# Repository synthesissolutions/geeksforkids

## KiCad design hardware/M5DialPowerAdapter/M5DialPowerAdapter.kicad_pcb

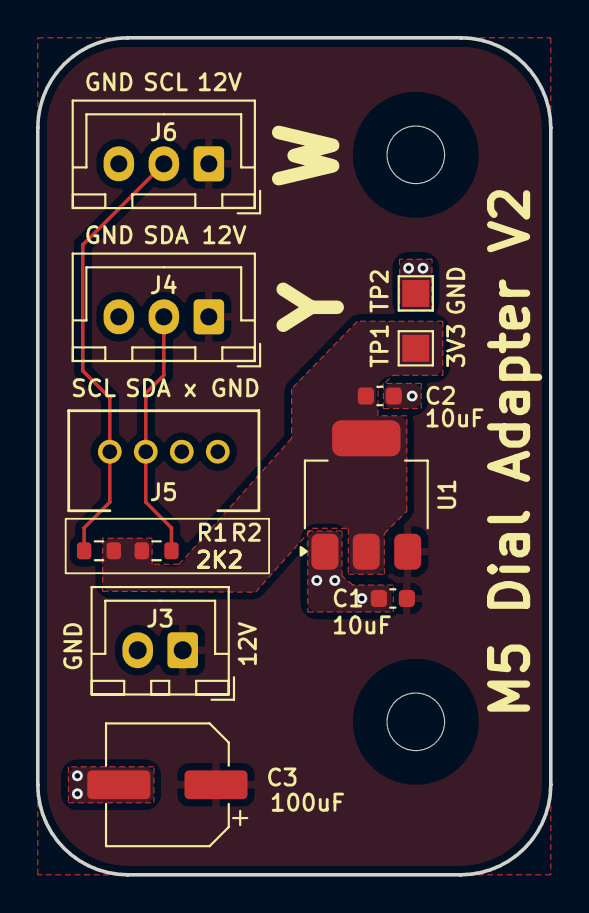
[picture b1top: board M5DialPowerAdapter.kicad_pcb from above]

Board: 2 copper layers, 28.5 x 46.5 mm, 14 parts (0 on the bottom side), 5 nets.

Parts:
C1, C2: 10uF; C_0603_1608Metric
C3: 100uF; CP_Elec_6.3x7.7
H1, H2: MountingHole_3.2mm_M3
J3: M5Dial Power; JST_XH_B2B-XH-A_1x02_P2.50mm_Vertical
J4: JST XH SCA; JST_XH_B3B-XH-A_1x03_P2.50mm_Vertical
J5: Grove I2C; CONN_110990030_SEE
J6: JST XH SCL; JST_XH_B3B-XH-A_1x03_P2.50mm_Vertical
R1, R2: 2K2; R_0603_1608Metric
TP1: 3V3; TestPoint_Pad_1.5x1.5mm
TP2: GND; TestPoint_Pad_1.5x1.5mm
U1: AMS1117-3.3; SOT-223-3_TabPin2

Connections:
+3V3: C2.1, R1.2, R2.2, TP1.1, U1.2 (VO)
+12V: C1.1, C3.1, J3.1, J4.1, J6.1, U1.3 (VI)
GND: C1.2, C2.2, C3.2, J3.2, J4.3, J5.4, J6.3, TP2.1, U1.1 (GND)
SCL: J5.1, J6.2, R1.1
SDA: J4.2, J5.2, R2.1

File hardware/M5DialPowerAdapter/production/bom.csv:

Designator,Footprint,Quantity,Value,LCSC Part #
"C1, C2",0603,2,10uF,C96446
C3,CP_Elec_6.3x7.7,1,100uF,C179802
J3,JST_XH_B2B-XH-A_1x02_P2.50mm_Vertical,1,M5Dial Power,
J4,JST_XH_B3B-XH-A_1x03_P2.50mm_Vertical,1,JST XH SCA,
J5,CONN_110990030_SEE,1,Grove I2C,
J6,JST_XH_B3B-XH-A_1x03_P2.50mm_Vertical,1,JST XH SCL,
"R1, R2",0603,2,2K2,C4190
TP1,TestPoint_Pad_1.5x1.5mm,1,3V3,
TP2,TestPoint_Pad_1.5x1.5mm,1,GND,
U1,SOT-223-3_TabPin2,1,AMS1117-3.3,C5120765

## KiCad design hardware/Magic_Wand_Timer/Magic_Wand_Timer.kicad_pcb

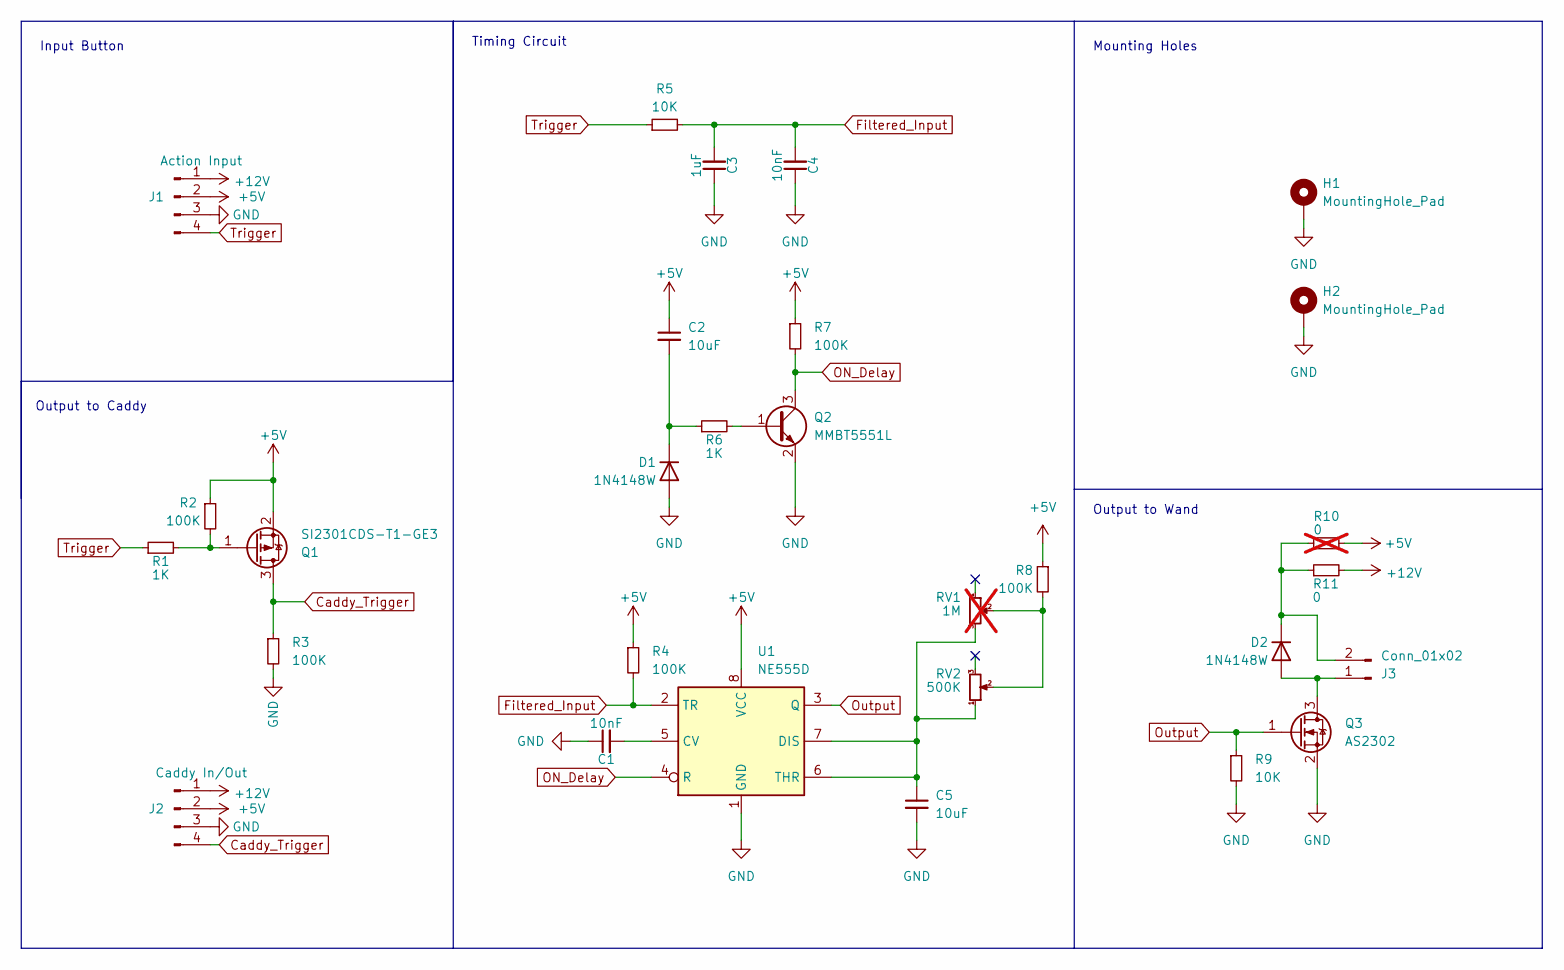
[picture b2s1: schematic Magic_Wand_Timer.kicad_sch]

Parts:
C1, C4: 10nF; C_0805_2012Metric; MPN C1710
C2, C5: 10uF; C_0805_2012Metric; MPN C15850
C3: 1uF; C_0805_2012Metric; MPN C28323
D1, D2: 1N4148W; D_SOD-123; MPN C81598
H1, H2: MountingHole_Pad; MountingHole_2.5mm_Pad
J1: Action Input; JST_XH_B4B-XH-A_1x04_P2.50mm_Vertical
J2: Caddy In/Out; JST_XH_B4B-XH-A_1x04_P2.50mm_Vertical
J3: Conn_01x02; JST_XH_B2B-XH-A_1x02_P2.50mm_Vertical
Q1: SI2301CDS-T1-GE3; SOT-23; MPN C10487
Q2: MMBT5551L; SOT-23; MPN C2145
Q3: AS2302; SOT-23; MPN C20917
R1, R6: 1K; R_0805_2012Metric; MPN C17513
R2, R3, R4, R7, R8: 100K; R_0805_2012Metric; MPN C149504
R5, R9: 10K; R_0805_2012Metric; MPN C17414
R10: 0; R_0805_2012Metric; MPN C17477; not fitted
R11: 0; R_0805_2012Metric; MPN C17477
RV1: 1M; Potentiometer_Piher_PT-6-V_Vertical; not fitted
RV2: 500K; Potentiometer_Bourns_TC33X_Vertical; MPN C128558
U1: NE555D; SOIC-8_3.9x4.9mm_P1.27mm; MPN C7593

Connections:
+5V: C2.1, J1.2, J2.2, Q1.2 (S), R2.1, R4.1, R7.1, R8.1, R10.1, U1.8 (VCC)
+12V: J1.1, J2.1, R11.2
Caddy_Trigger: J2.4, Q1.3 (D), R3.1
Filtered_Input: C3.2, C4.2, R4.2, R5.2, U1.2 (TR)
GND: C1.1, C3.1, C4.1, C5.2, D1.2 (A), H1.1, H2.1, J1.3, J2.3, Q2.2 (E), Q3.2 (S), R3.2, R9.2, U1.1 (GND)
unnamed: C2.2, D1.1 (K), R6.1
unnamed: D2.2 (A), J3.1, Q3.3 (D)
unnamed: D2.1 (K), J3.2, R10.2, R11.1
unnamed: Q1.1 (G), R1.2, R2.2
unnamed: Q2.1 (B), R6.2
unnamed: R8.2, RV1.2, RV2.2
unnamed: C1.2, U1.5 (CV)
unnamed: C5.1, RV1.3, RV2.1, U1.6 (THR), U1.7 (DIS)
ON_Delay: Q2.3 (C), R7.2, U1.4 (R)
Output: Q3.1 (G), R9.1, U1.3 (Q)
Trigger: J1.4, R1.1, R5.1

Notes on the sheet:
Timing Circuit
Mounting Holes
Output to Wand
Input Button
Output to Caddy

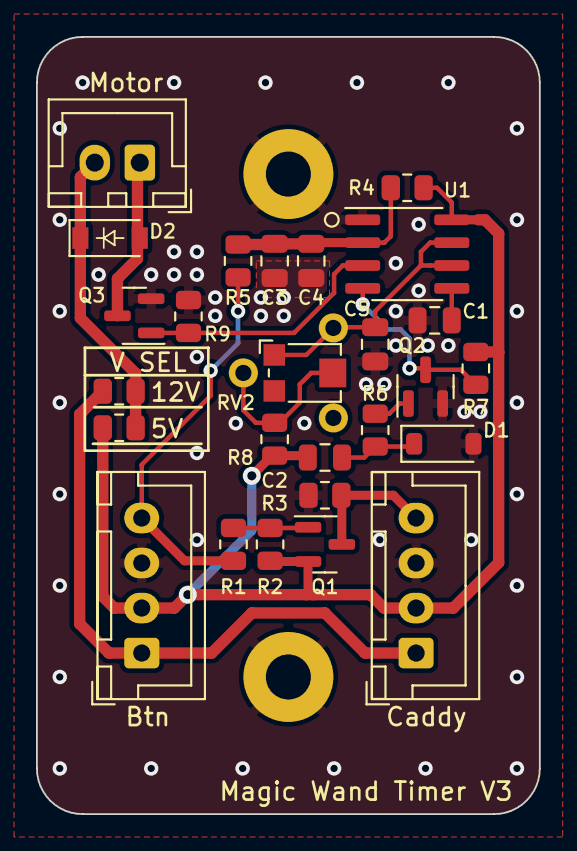
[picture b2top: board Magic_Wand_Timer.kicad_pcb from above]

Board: 2 copper layers, 27.9 x 43.2 mm, 29 parts (1 on the bottom side), 16 nets.

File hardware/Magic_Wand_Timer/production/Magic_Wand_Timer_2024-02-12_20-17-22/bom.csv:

Designator,Footprint,Quantity,Value,LCSC Part #
"C1, C4",0805,2,10nF,C1710
"C2, C5",0805,2,10uF,C15850
C3,0805,1,1uF,C28323
"D1, D2",D_SOD-123,2,1N4148W,C81598
"H1, H2",MountingHole_2.5mm_Pad,2,MountingHole_Pad,
J3,JST_XH_B2B-XH-A_1x02_P2.50mm_Vertical,1,Conn_01x02,
Q1,SOT-23,1,SI2301CDS-T1-GE3,C10487
Q2,SOT-23,1,MMBT5551L,C2145
Q3,SOT-23,1,AS2302,C20917
"R1, R6",0805,2,1K,C17513
R11,0805,1,0,C17477
"R2, R3, R4, R7, R8",0805,5,100K,C149504
"R5, R9",0805,2,10K,C17414
RV1,Potentiometer_Piher_PT-6-V_Vertical,1,1M,
RV2,Potentiometer_Bourns_TC33X_Vertical,1,500K,C128558
U1,SOIC-8_3.9x4.9mm_P1.27mm,1,NE555D,C7593

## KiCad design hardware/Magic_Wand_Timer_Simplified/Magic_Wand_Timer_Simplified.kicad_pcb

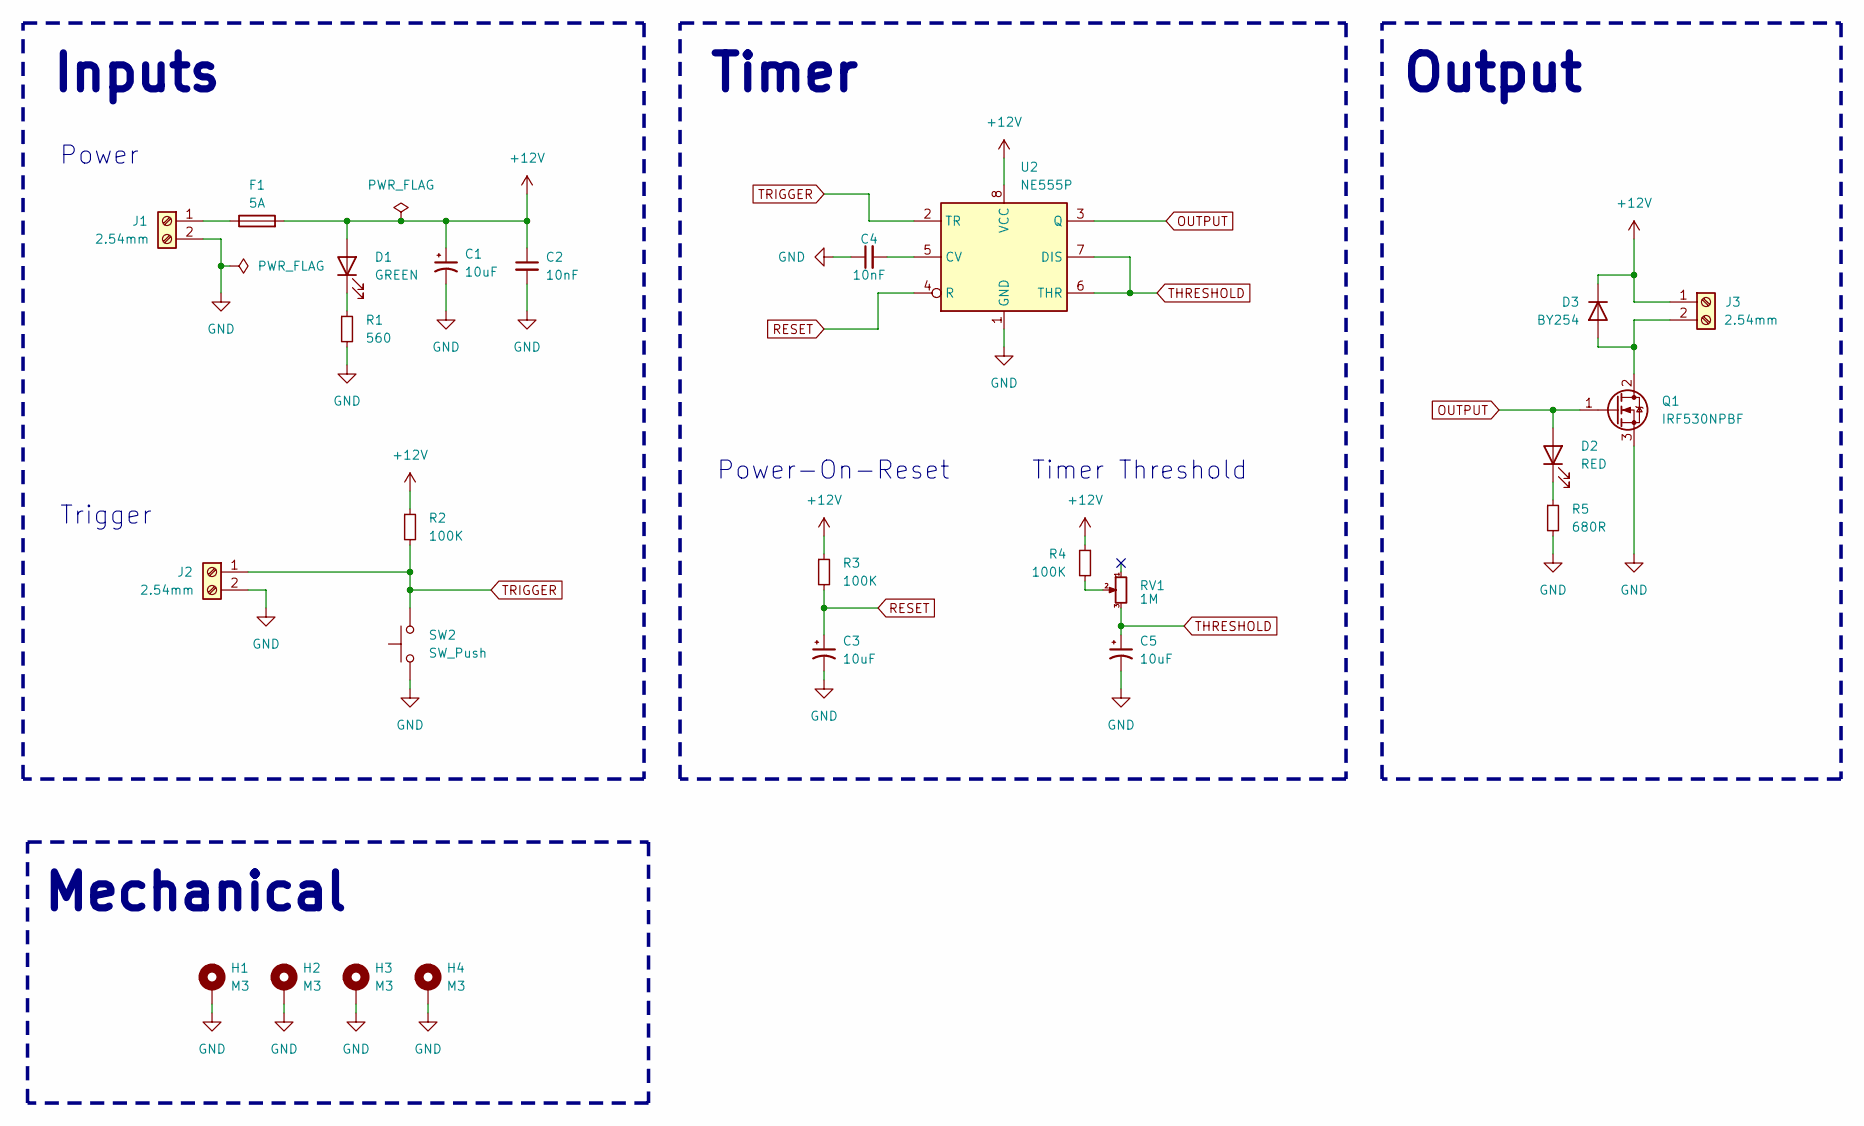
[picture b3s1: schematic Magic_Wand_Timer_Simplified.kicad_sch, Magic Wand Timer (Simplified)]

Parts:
C1, C3, C5: 10uF; C_Radial_D5.0mm_H11.0mm_P2.00mm; MPN C503219
C2, C4: 10nF; C_Disc_D3.8mm_W2.6mm_P2.50mm; MPN C2832505
D1: GREEN; LED_D5.0mm_Clear
D2: RED; LED_D5.0mm_Clear
D3: BY254; D_DO-201AD_P12.70mm_Horizontal; MPN C5148433
F1: 5A; Fuseholder_Clip-5x20mm_Littelfuse_111_Lateral_P18.80x5.00mm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; MPN C142664 + 2x C151075
H1, H2, H3, H4: M3; MountingHole_3.2mm_M3_Pad_Via
J1, J2, J3: 2.54mm; TerminalBlock_bornier-2_P5.08mm
Q1: IRF530NPBF; TO-220-3_Horizontal_TabDown; MPN C2565
R1: 560; R_Axial_DIN0309_L9.0mm_D3.2mm_P12.70mm_Horizontal
R2, R3, R4: 100K; R_Axial_DIN0309_L9.0mm_D3.2mm_P12.70mm_Horizontal
R5: 680R; R_Axial_DIN0309_L9.0mm_D3.2mm_P12.70mm_Horizontal
RV1: 1M; Potentiometer_Bourns_3386F_Vertical
SW2: SW_Push; SW_PUSH_6mm
U2: NE555P; DIP-8_W7.62mm; MPN C20616346

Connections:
+12V: C1.1, C2.1, D1.2 (A), D3.1 (K), F1.2, J3.1, R2.1, R3.1, R4.1, U2.8 (VCC)
GND: C1.2, C2.2, C3.2, C4.1, C5.2, H1.1, H2.1, H3.1, H4.1, J1.2, J2.2, Q1.3 (S), R1.2, R5.2, SW2.1, U2.1 (GND)
unnamed: D1.1 (K), R1.1
unnamed: D2.1 (K), R5.1
unnamed: D3.2 (A), J3.2, Q1.2 (D)
unnamed: F1.1, J1.1
unnamed: R4.2, RV1.2
unnamed: C4.2, U2.5 (CV)
OUTPUT: D2.2 (A), Q1.1 (G), U2.3 (Q)
RESET: C3.1, R3.2, U2.4 (R)
THRESHOLD: C5.1, RV1.3, U2.6 (THR), U2.7 (DIS)
TRIGGER: J2.1, R2.2, SW2.2, U2.2 (TR)

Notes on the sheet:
Inputs
Timer
Timer Threshold
Power
Mechanical
Output
Trigger
Power-On-Reset

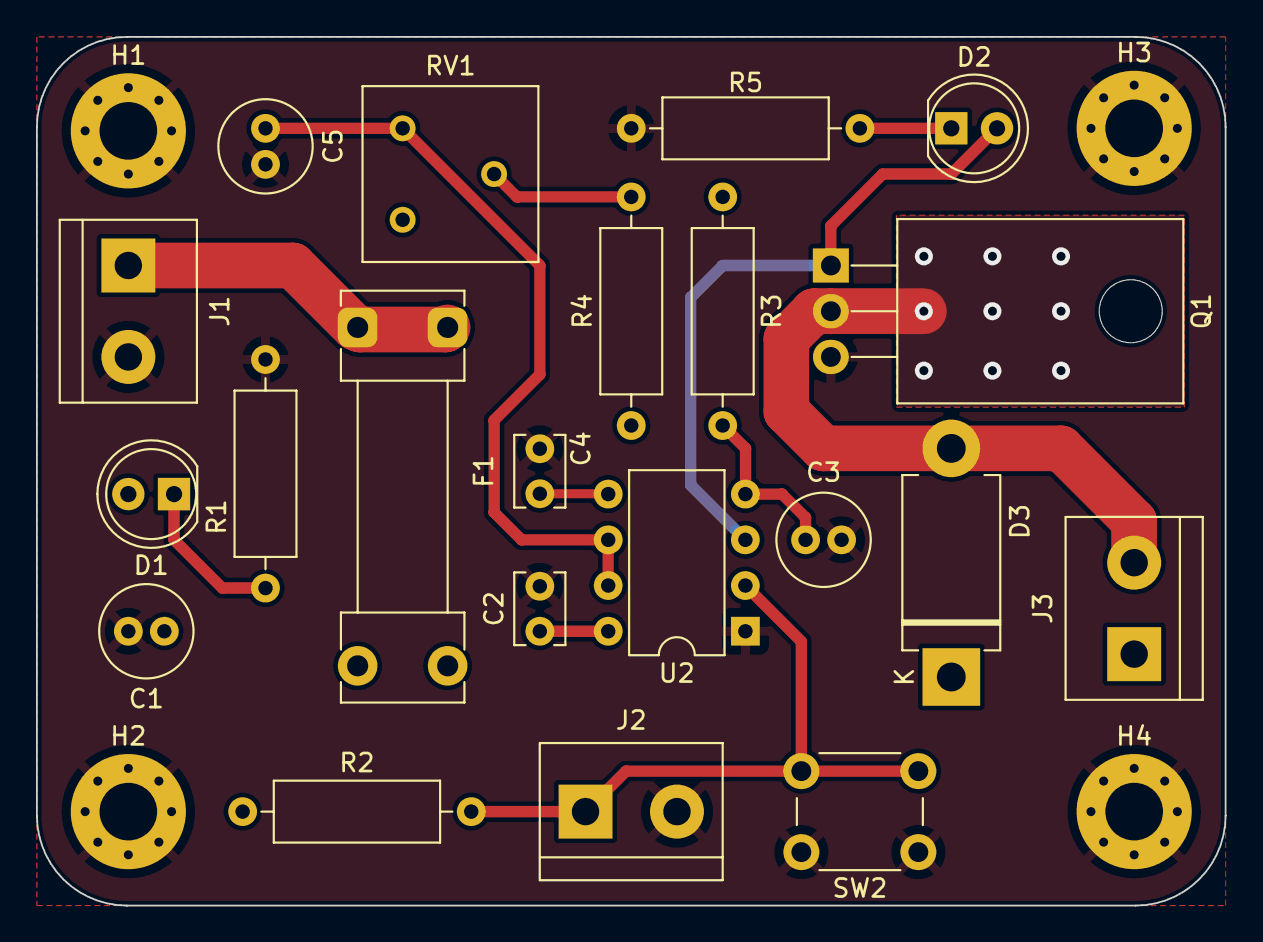
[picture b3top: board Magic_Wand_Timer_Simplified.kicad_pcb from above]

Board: 4 copper layers, 66.0 x 48.3 mm, 25 parts (0 on the bottom side), 12 nets.

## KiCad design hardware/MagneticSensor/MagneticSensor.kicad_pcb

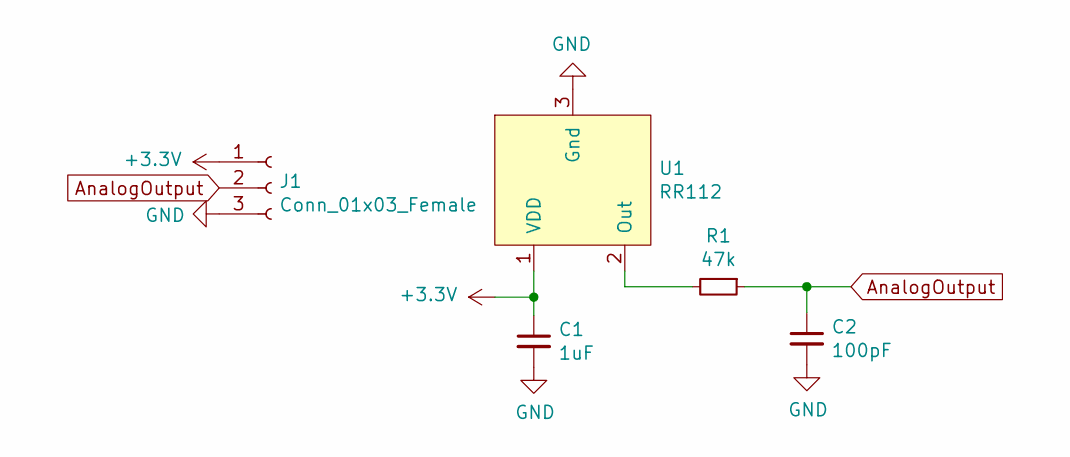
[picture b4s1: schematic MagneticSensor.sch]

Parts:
C1: 1uF; C_0805_2012Metric_Pad1.15x1.40mm_HandSolder
C2: 100pF; C_0805_2012Metric_Pad1.15x1.40mm_HandSolder
J1: Conn_01x03_Female; PinHeader_1x03_P2.54mm_Vertical
R1: 47k; R_0805_2012Metric_Pad1.15x1.40mm_HandSolder
U1: RR112; SOT-23_Handsoldering

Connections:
+3V3: C1.1, J1.1, U1.1 (VDD)
AnalogOutput: C2.1, J1.2, R1.1
GND: C1.2, C2.2, J1.3, U1.3 (Gnd)
unnamed: R1.2, U1.2 (Out)

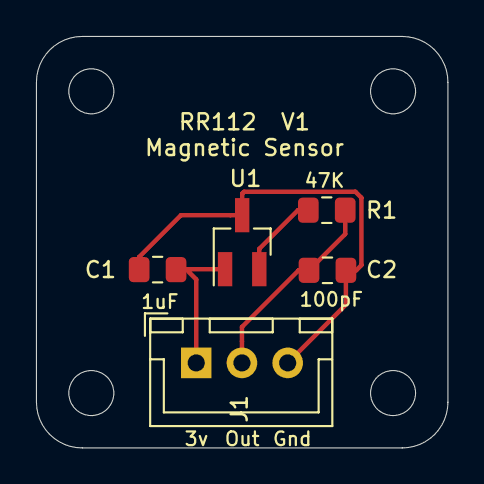
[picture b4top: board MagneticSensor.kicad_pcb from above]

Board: 2 copper layers, 22.9 x 22.9 mm, 5 parts (0 on the bottom side), 4 nets.

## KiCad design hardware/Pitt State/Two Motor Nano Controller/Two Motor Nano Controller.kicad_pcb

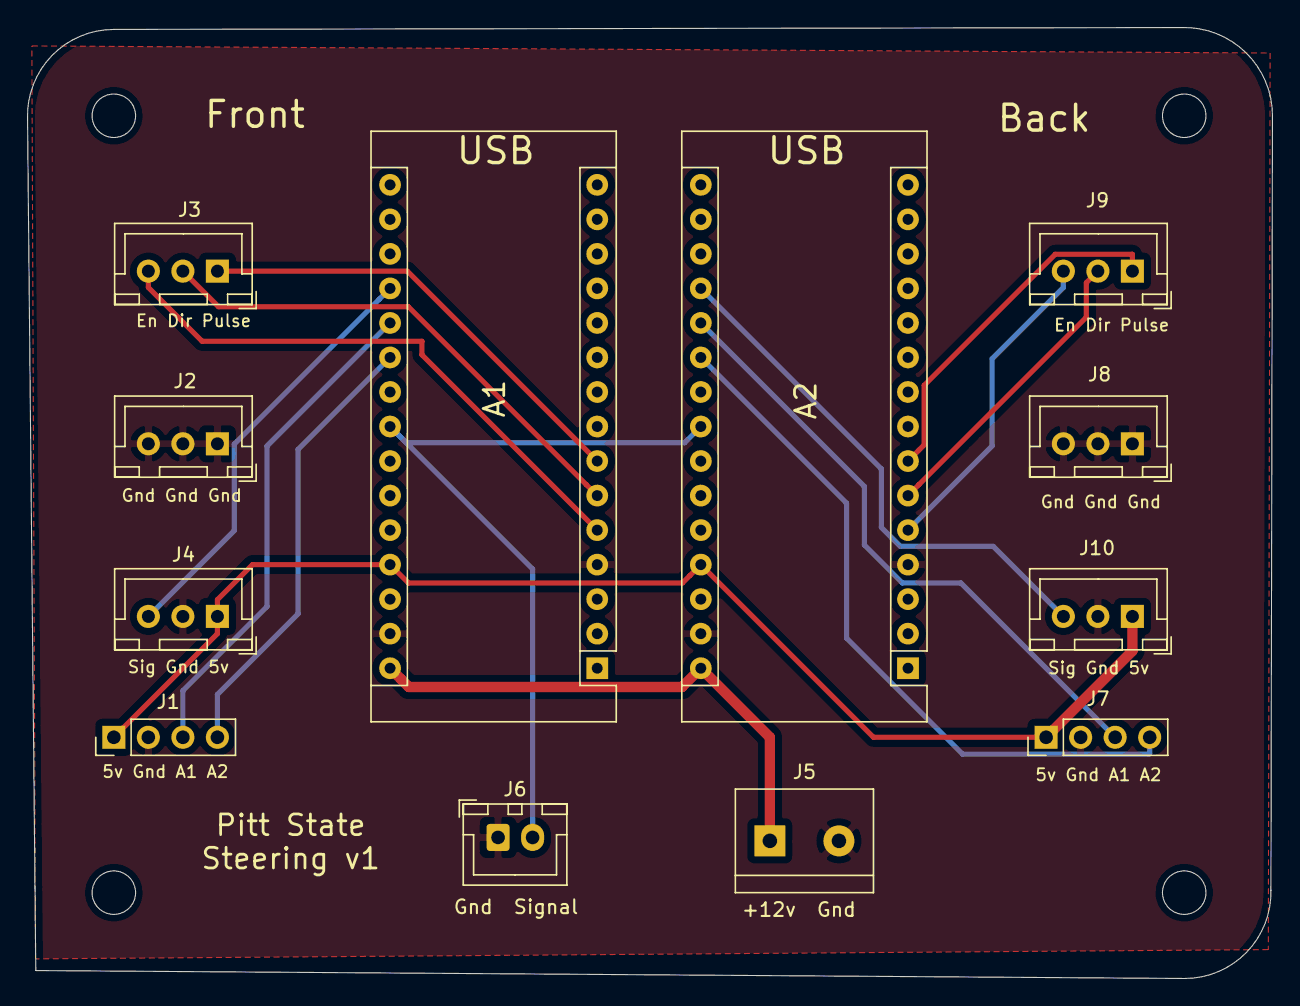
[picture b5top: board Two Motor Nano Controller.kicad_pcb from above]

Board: 2 copper layers, 91.6 x 70.0 mm, 12 parts (0 on the bottom side), 16 nets.

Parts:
A1, A2: Arduino_Nano_v3.x; Arduino_Nano
J1: Additiona Inputs Front; PinHeader_1x04_P2.54mm_Vertical
J2, J8: Stepper Minus Front; JST_XH_B3B-XH-A_1x03_P2.54mm_Vertical
J3: Stepper Plus Front; JST_XH_B3B-XH-A_1x03_P2.54mm_Vertical
J4, J10: Limit Switch Front; JST_XH_B3B-XH-A_1x03_P2.54mm_Vertical
J5: 12v Power; TerminalBlock_bornier-2_P5.08mm
J6: Analog Steering; JST_XH_B2B-XH-A_1x02_P2.54mm_Vertical
J7: Additiona Inputs Back; PinHeader_1x04_P2.54mm_Vertical
J9: Stepper Plus Back; JST_XH_B3B-XH-A_1x03_P2.54mm_Vertical

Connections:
+5V: A1.27, A2.27, J1.1, J4.1, J7.1, J10.1
+12V: A1.30, A2.30, J5.1
A1Back: A2.20, J7.3
A1Front: A1.20, J1.3
A2Back: A2.21, J7.4
A2Front: A1.21, J1.4
DirBack: A2.6, J9.2
DirFront: A1.6, J3.2
EnableBack: A2.5, J9.3
EnableFront: A1.5, J3.3
GND: A1.4, A1.29, A2.4, A2.29, J1.2, J2.1, J2.2, J2.3, J4.2, J5.2, J6.1, J7.2, J8.1, J8.2, J8.3, J10.2
LimitSwitchBack: A2.19, J10.3
LimitSwitchFront: A1.19, J4.3
PulseBack: A2.7, J9.1
PulseFront: A1.7, J3.1
SteeringSignal: A1.23, A2.23, J6.2

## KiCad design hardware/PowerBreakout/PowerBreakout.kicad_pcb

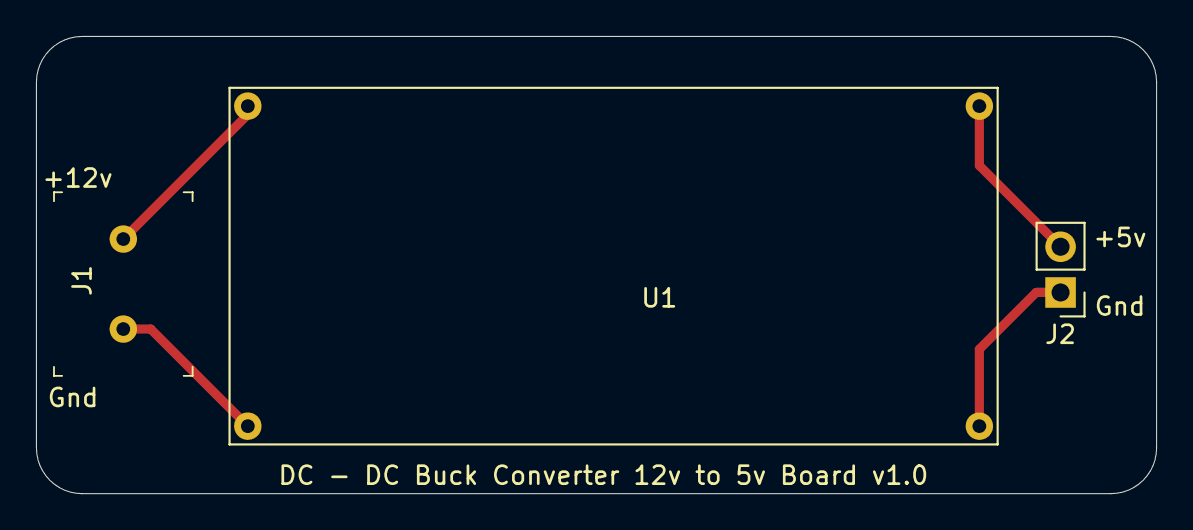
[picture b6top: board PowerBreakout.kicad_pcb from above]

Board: 2 copper layers, 62.2 x 25.4 mm, 3 parts (0 on the bottom side), 4 nets.

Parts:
J1: Screw_Terminal_01x02; Term_Block_1x2_P5mm
J2: Conn_01x02_Male; PinHeader_1x02_P2.54mm_Vertical
U1: LM2596Adj

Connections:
unnamed: J1.1, U1.2
unnamed: J1.2, U1.1
unnamed: J2.1, U1.4
unnamed: J2.2, U1.3

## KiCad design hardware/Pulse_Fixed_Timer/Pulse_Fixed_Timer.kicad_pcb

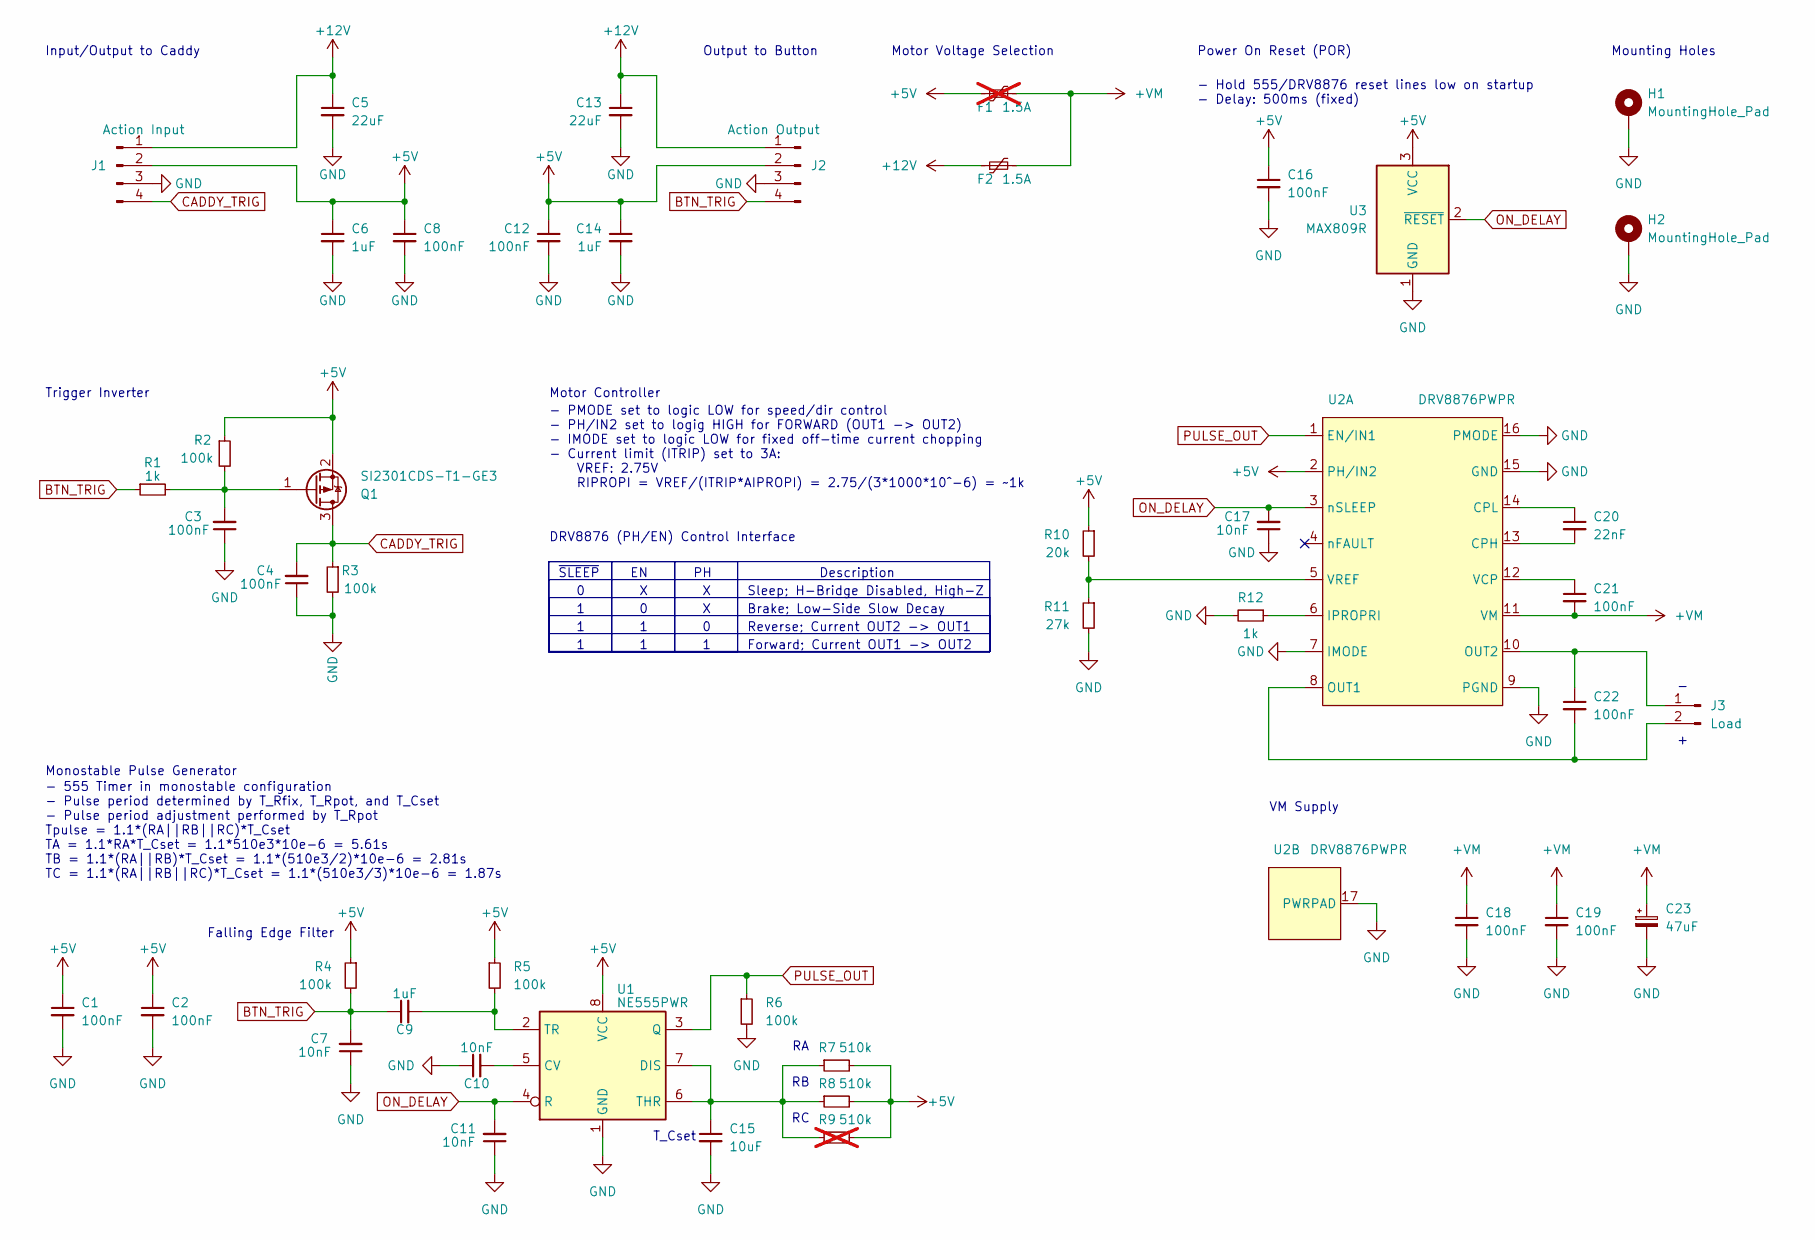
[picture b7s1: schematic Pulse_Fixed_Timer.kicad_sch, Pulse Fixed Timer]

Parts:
C1, C2, C3, C4, C8, C12, C16, C18, C19, C21, C22: 100nF; C_0402_1005Metric; MPN C307331
C5, C13: 22uF; C_0805_2012Metric; MPN C45783
C6, C9, C14: 1uF; C_0402_1005Metric; MPN C52923
C7, C10, C11, C17: 10nF; C_0402_1005Metric; MPN C15195
C15: 10uF; C_0603_1608Metric; MPN C96446
C20: 22nF; C_0402_1005Metric; MPN C1532
C23: 47uF; CP_Elec_6.3x5.4; MPN C3001213
F1: 1.5A; Fuse_1210_3225Metric; MPN C22374902; not fitted
F2: 1.5A; Fuse_1210_3225Metric; MPN C22374902
H1, H2: MountingHole_Pad; MountingHole_2.5mm_Pad
J1: Action Input; JST_XH_B4B-XH-A_1x04_P2.50mm_Vertical
J2: Action Output; JST_XH_B4B-XH-A_1x04_P2.50mm_Vertical
J3: Load; JST_XH_B2B-XH-A_1x02_P2.50mm_Vertical
Q1: SI2301CDS-T1-GE3; SOT-23; MPN C10487
R1, R12: 1k; R_0402_1005Metric; MPN C11702
R2, R3, R4, R5, R6: 100k; R_0402_1005Metric; MPN C25741
R7, R8: 510k; R_0603_1608Metric; MPN C23192
R9: 510k; R_0603_1608Metric; MPN C23192; not fitted
R10: 20k; R_0402_1005Metric; MPN C25765
R11: 27k; R_0402_1005Metric; MPN C25771
U1: NE555PWR; TSSOP-8_4.4x3mm_P0.65mm; MPN C105643
U2: DRV8876PWPR; HTSSOP-16-1EP_4.4x5mm_P0.65mm_EP3.4x5mm_Mask2.46x2.31mm; MPN C575551
U3: MAX809R; SOT-23; MPN C19631717

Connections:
+5V: C1.1, C2.1, C6.1, C8.1, C12.1, C14.1, C16.1, F1.1, J1.2, J2.2, Q1.2 (S), R2.1, R4.1, R5.1, R7.2, R8.2, R9.2, R10.1, U1.8 (VCC), U2.2 (PH/IN2), U3.3 (VCC)
+12V: C5.1, C13.1, F2.1, J1.1, J2.1
+VM: C18.1, C19.1, C21.2, C23.1, F1.2, F2.2, U2.11 (VM)
BTN_TRIG: C7.2, C9.1, J2.4, R1.1, R4.2
CADDY_TRIG: C4.2, J1.4, Q1.3 (D), R3.1
GND: C1.2, C2.2, C3.1, C4.1, C5.2, C6.2, C7.1, C8.2, C10.1, C11.1, C12.2, C13.2, C14.2, C15.2, C16.2, C17.1, C18.2, C19.2, C23.2, H1.1, H2.1, J1.3, J2.3, R3.2, R6.2, R11.2, R12.2, U1.1 (GND), U2.7 (IMODE), U2.9 (PGND), U2.15 (GND), U2.16 (PMODE), U2.17 (PWRPAD), U3.1 (GND)
unnamed: C22.1, J3.1, U2.10 (OUT2)
unnamed: C22.2, J3.2, U2.8 (OUT1)
unnamed: C3.2, Q1.1 (G), R1.2, R2.2
unnamed: C10.2, U1.5 (CV)
unnamed: C15.1, R7.1, R8.1, R9.1, U1.6 (THR), U1.7 (DIS)
unnamed: C9.2, R5.2, U1.2 (TR)
unnamed: C20.2, U2.13 (CPH)
unnamed: C20.1, U2.14 (CPL)
unnamed: R12.1, U2.6 (IPROPRI)
unnamed: C21.1, U2.12 (VCP)
unnamed: R10.2, R11.1, U2.5 (VREF)
ON_DELAY: C11.2, C17.2, U1.4 (R), U2.3 (nSLEEP), U3.2 (~RESET)
PULSE_OUT: R6.1, U1.3 (Q), U2.1 (EN/IN1)

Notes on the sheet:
Description
- 555 Timer in monostable configuration - Pulse period determined by T_Rfix, T_Rpot, and T_Cset - Pulse period adjustment performed by T_Rpot Tpulse = 1.1*(RA||RB||RC)*T_Cset TA = 1.1*RA*T_Cset = 1.1*510e3*10e-6 = 5.61s TB = 1.1*(RA||RB)*T_Cset = 1.1*(510e3/2)*10e-6 = 2.81s TC = 1.1*(RA||RB||RC)*T_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
Brake; Low-Side Slow Decay
Monostable Pulse Generator
Trigger Inverter
Reverse; Current OUT2 -> OUT1
- PMODE set to logic LOW for speed/dir control - PH/IN2 set to logig HIGH for FORWARD (OUT1 -> OUT2) - IMODE set to logic LOW for fixed off-time current chopping - Current limit (ITRIP) set to 3A: VREF: 2.75V RIPROPI = VREF/(ITRIP*AIPROPI) = 2.75/(3*1000*10^-6) = ~1k
DRV8876 (PH/EN) Control Interface
Motor Voltage Selection
~{SLEEP}
Forward; Current OUT1 -> OUT2
Falling Edge Filter
- Hold 555/DRV8876 reset lines low on startup - Delay: 500ms (fixed)
Mounting Holes
VM Supply
Motor Controller
Output to Button
T_Cset
Sleep; H-Bridge Disabled, High-Z
Power On Reset (POR)
Input/Output to Caddy

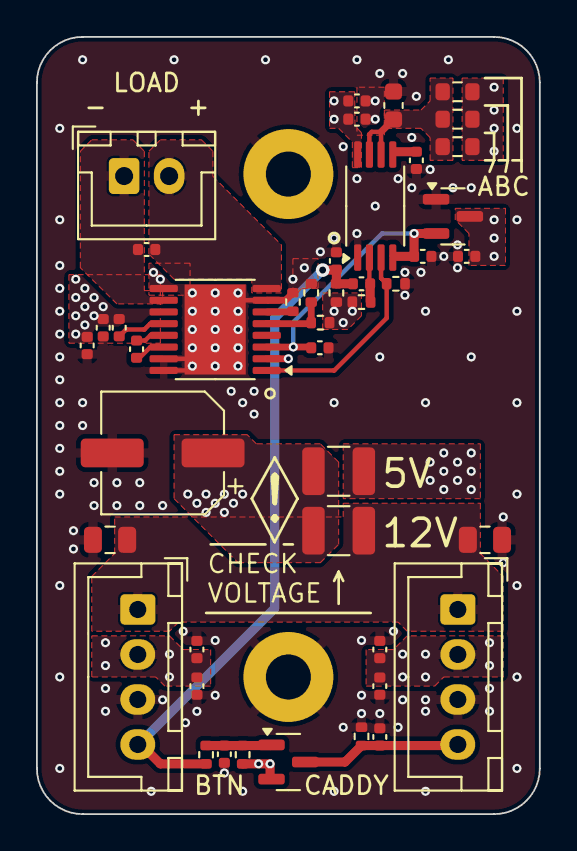
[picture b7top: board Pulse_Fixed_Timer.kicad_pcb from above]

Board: 4 copper layers, 27.9 x 43.2 mm, 46 parts (0 on the bottom side), 19 nets.

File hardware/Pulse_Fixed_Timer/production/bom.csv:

Designator,Footprint,Quantity,Value,LCSC Part #
"C1, C12, C16, C18, C19, C2, C21, C22, C3, C4, C8",0402,11,100nF,C307331
"C10, C11, C17, C7",0402,4,10nF, C15195
"C13, C5",0805,2,22uF,C45783
"C14, C6, C9",0402,3,1uF,C52923
C15,0603,1,10uF,C96446
C20,0402,1,22nF,C1532
C23,CP_Elec_6.3x5.4,1,47uF, C3001213
F2,1210,1,1.5A,C22374902
"H1, H2",MountingHole_2.5mm_Pad,2,MountingHole_Pad,
J3,JST_XH_B2B-XH-A_1x02_P2.50mm_Vertical,1,Load,
Q1,SOT-23,1,SI2301CDS-T1-GE3,C10487
"R1, R12",0402,2,1k,C11702
R10,0402,1,20k,C25765
R11,0402,1,27k,C25771
"R2, R3, R4, R5, R6",0402,5,100k,C25741
"R7, R8",0603,2,500k,
U1,TSSOP-8_4.4x3mm_P0.65mm,1,NE555PWR,C105643
U2,HTSSOP-16-1EP_4.4x5mm_P0.65mm_EP3.4x5mm_Mask2.46x2.31mm,1,DRV8876PWPR,C575551
U3,SOT-23,1,MAX809R,C19631717
